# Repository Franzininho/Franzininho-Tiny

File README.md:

# Franzininho Tiny
Repositório para Franzininho Tiny - Uma placa com attiny841 da família Franzinho

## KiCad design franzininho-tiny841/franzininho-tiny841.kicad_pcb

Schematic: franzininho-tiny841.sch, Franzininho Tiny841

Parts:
C1, C2: 10uF; C_0805_HandSoldering
D1, D2: 3V6; D_SOD-323_HandSoldering
D3: 1N4148; D_SOD-123F
D4, D5: LED; LED_0603_HandSoldering
J1: USB_B_Micro; USB_Micro-B_Molex-105017-0001
J2, J3: Conn_01x08; Pin_Header_Straight_1x08_Pitch2.54mm
R1: 1K5; R_0603_HandSoldering
R2, R3: 68R; R_0603_HandSoldering
R4, R5, R6: 1K; R_0603_HandSoldering
SW1: SW_Push; SW_SPST_B3U-1000P
U1: LP2985-5.0; SOT-23-5_HandSoldering
U2: ATtiny841-SSU; SOIC-14_N

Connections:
+5V: C2.1, D3.1, J3.1, R1.2, R4.2, R5.2, R6.1, U1.5 (VOUT), U2.1 (VCC)
+BATT: C1.1, J2.1, U1.1 (VIN), U1.3 (ON/~OFF~)
GNDREF: C1.2, C2.2, D1.2, D2.2, D4.1, J1.5, J1.6, J2.2, J3.2, SW1.1, U1.2 (GND), U2.14 (GND)
unnamed: D1.1, J1.3, R2.2
unnamed: D2.1, J1.2, R1.1, R3.2
unnamed: D4.2, R4.1
unnamed: D5.2, R5.1
PA0: J2.3, U2.13 (AREF/PA0)
PA1: J2.4, U2.12 (PA1)
PA2: J2.5, U2.11 (PA2)
PA3: J2.6, U2.10 (PA3)
PA4: J2.7, U2.9 (PA4)
PA5: J2.8, U2.8 (PA5)
PA6: J3.8, U2.7 (PA6)
PA7: J3.7, U2.6 (PA7)
PB0: J3.3, R2.1, U2.2 (XTAL1/PB0)
PB1: J3.4, R3.1, U2.3 (XTAL2/PB1)
PB2: D5.1, J3.6, U2.5 (PB2)
PB3: J3.5, R6.2, SW1.2, U2.4 (~RESET~/PB3)
VBUS: D3.2, J1.1

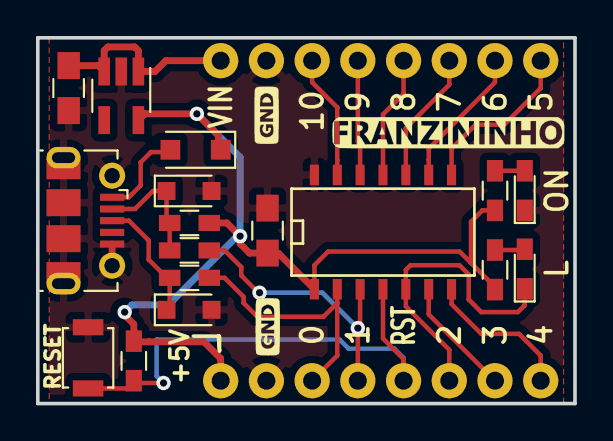
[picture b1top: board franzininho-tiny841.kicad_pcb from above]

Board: 2 copper layers, 29.8 x 20.3 mm, 19 parts (0 on the bottom side), 20 nets.

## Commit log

2019-03-06 doc1
    PDF e imagens da placa
2019-03-08 Commit do projeto e Licença
    Projeto e licença
